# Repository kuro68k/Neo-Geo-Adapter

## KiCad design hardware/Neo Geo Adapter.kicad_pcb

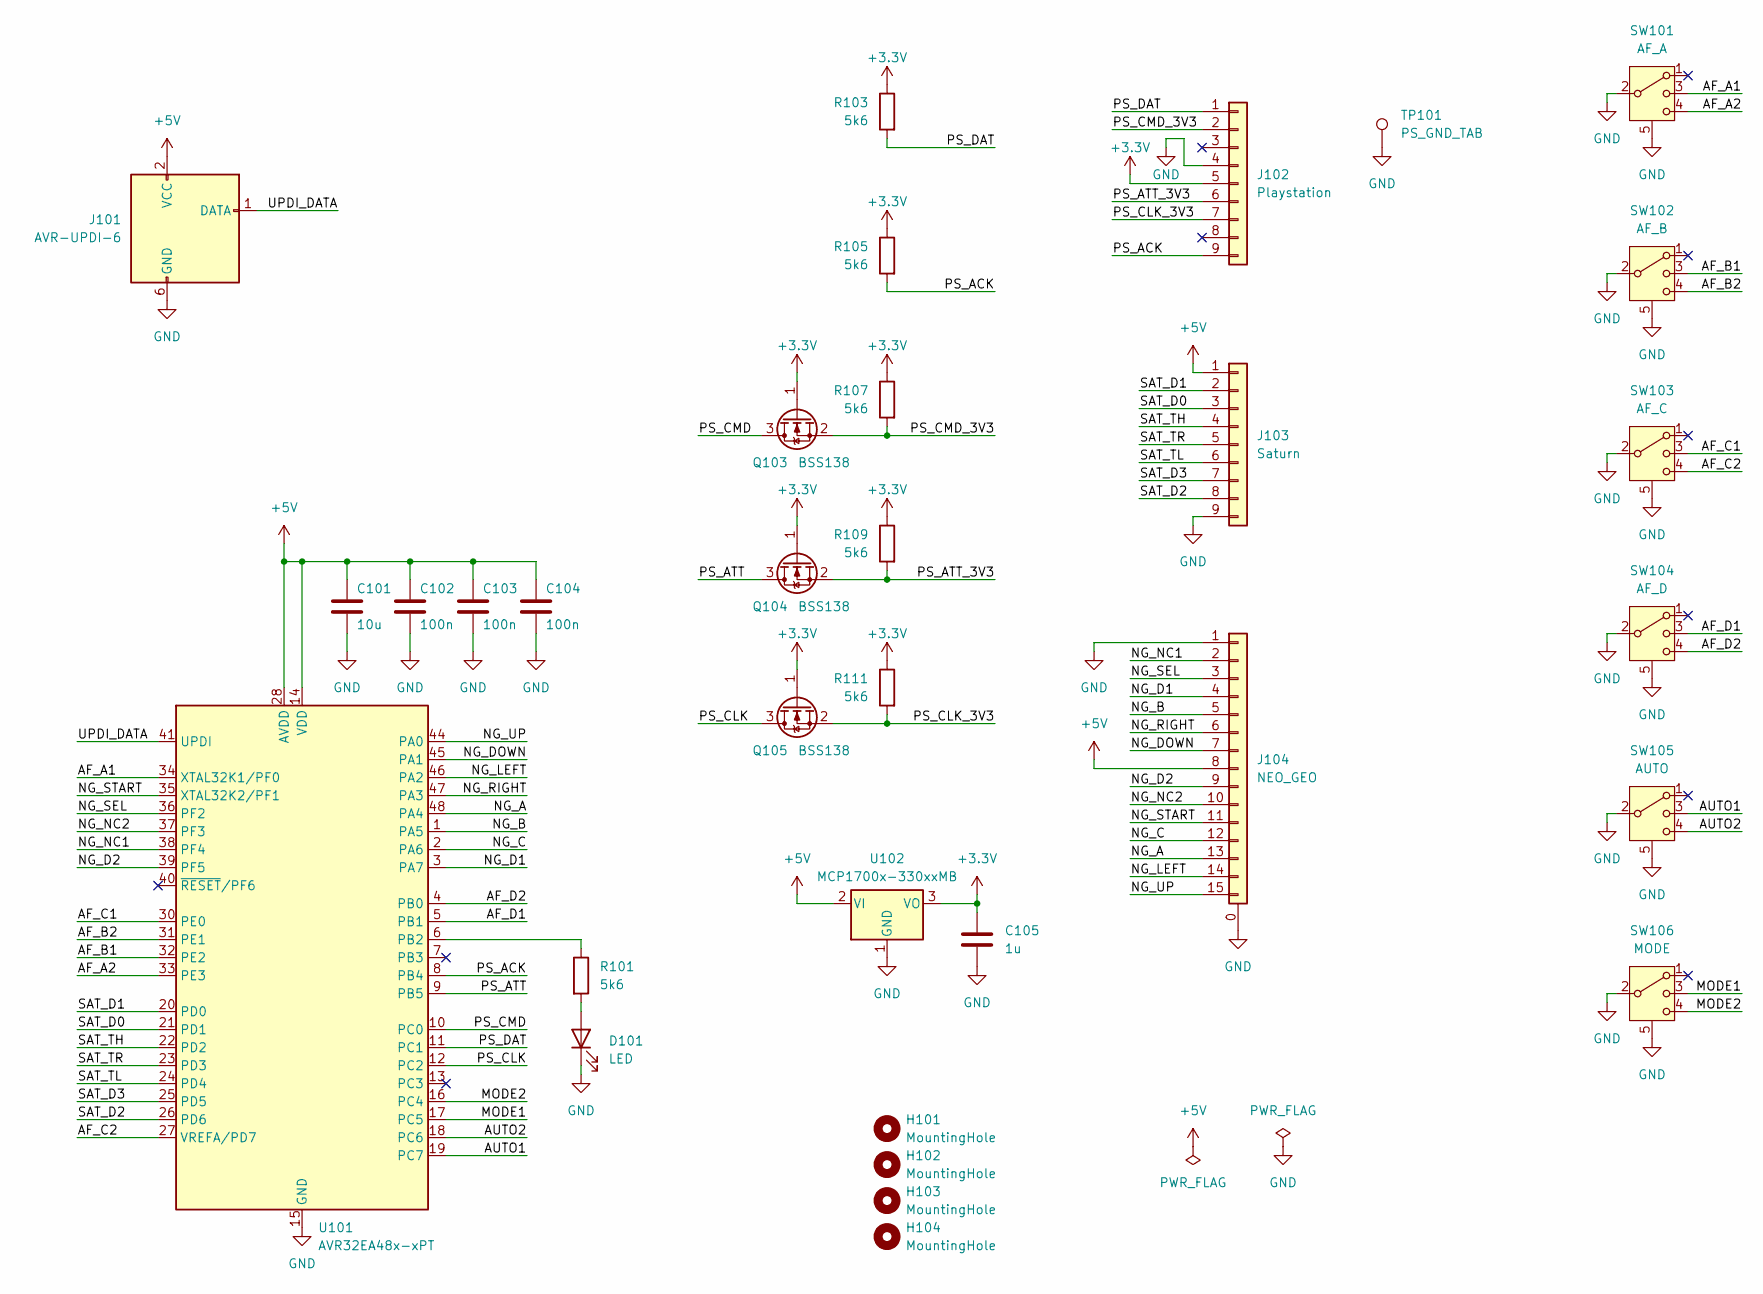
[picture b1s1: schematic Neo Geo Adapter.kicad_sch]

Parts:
C101: 10u; C_0805_2012Metric_Pad1.18x1.45mm_HandSolder
C102, C103, C104: 100n; C_0805_2012Metric_Pad1.18x1.45mm_HandSolder
C105: 1u; C_0805_2012Metric_Pad1.18x1.45mm_HandSolder
D101: LED; LED_0805_2012Metric_Pad1.15x1.40mm_HandSolder
H101, H102, H103, H104: MountingHole; MountingHole_3.2mm_M3
J101: AVR-UPDI-6; PinHeader_2x03_P1.27mm_Vertical_SMD
J102: Playstation; Sony_Playstation
J103: Saturn; Sega_Saturn
J104: NEO_GEO; DSUB-15_Female_Horizontal_P2.77x2.84mm_EdgePinOffset7.70mm_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; MPN Amphenol L77SDA15SA4CH4F
Q103, Q104, Q105: BSS138; SOT-23
R101, R103, R105, R107, R109, R111: 5k6; R_0805_2012Metric_Pad1.20x1.40mm_HandSolder
SW101: AF_A; XKB_SS13D75
SW102: AF_B; XKB_SS13D75
SW103: AF_C; XKB_SS13D75
SW104: AF_D; XKB_SS13D75
SW105: AUTO; XKB_SS13D75
SW106: MODE; XKB_SS13D75
TP101: PS_GND_TAB; TestPoint_THTPad_D2.5mm_Drill1.2mm
U101: AVR32EA48x-xPT; TQFP-48_7x7mm_P0.5mm
U102: MCP1700x-330xxMB; SOT-89-3

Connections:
+3.3V: C105.1, J102.5, Q103.1 (G), Q104.1 (G), Q105.1 (G), R103.1, R105.1, R107.1, R109.1, R111.1, U102.3 (VO)
+5V: C101.1, C102.1, C103.1, C104.1, J101.2 (VCC), J103.1, J104.8, U101.14 (VDD), U101.28 (AVDD), U101.42 (VDD), U102.2 (VI)
/AF_A1: SW101.3, U101.34 (XTAL32K1/PF0)
/AF_A2: SW101.4, U101.33 (PE3)
/AF_B1: SW102.3, U101.32 (PE2)
/AF_B2: SW102.4, U101.31 (PE1)
/AF_C1: SW103.3, U101.30 (PE0)
/AF_C2: SW103.4, U101.27 (VREFA/PD7)
/AF_D1: SW104.3, U101.5 (PB1)
/AF_D2: SW104.4, U101.4 (PB0)
/AUTO1: SW105.3, U101.19 (PC7)
/AUTO2: SW105.4, U101.18 (PC6)
/MODE1: SW106.3, U101.17 (PC5)
/MODE2: SW106.4, U101.16 (PC4)
/NG_A: J104.13, U101.48 (PA4)
/NG_B: J104.5, U101.1 (PA5)
/NG_C: J104.12, U101.2 (PA6)
/NG_D1: J104.4, U101.3 (PA7)
/NG_D2: J104.9, U101.39 (PF5)
/NG_DOWN: J104.7, U101.45 (PA1)
/NG_LEFT: J104.14, U101.46 (PA2)
/NG_NC1: J104.2, U101.38 (PF4)
/NG_NC2: J104.10, U101.37 (PF3)
/NG_RIGHT: J104.6, U101.47 (PA3)
/NG_SEL: J104.3, U101.36 (PF2)
/NG_START: J104.11, U101.35 (XTAL32K2/PF1)
/NG_UP: J104.15, U101.44 (PA0)
/PS_ACK: J102.9, R105.2, U101.8 (PB4)
/PS_ATT: Q104.3 (D), U101.9 (PB5)
/PS_ATT_3V3: J102.6, Q104.2 (S), R109.2
/PS_CLK: Q105.3 (D), U101.12 (PC2)
/PS_CLK_3V3: J102.7, Q105.2 (S), R111.2
/PS_CMD: Q103.3 (D), U101.10 (PC0)
/PS_CMD_3V3: J102.2, Q103.2 (S), R107.2
/PS_DAT: J102.1, R103.2, U101.11 (PC1)
/SAT_D0: J103.3, U101.21 (PD1)
/SAT_D1: J103.2, U101.20 (PD0)
/SAT_D2: J103.8, U101.26 (PD6)
/SAT_D3: J103.7, U101.25 (PD5)
/SAT_TH: J103.4, U101.22 (PD2)
/SAT_TL: J103.6, U101.24 (PD4)
/SAT_TR: J103.5, U101.23 (PD3)
/UPDI_DATA: J101.1 (DATA), U101.41 (UPDI)
GND: C101.2, C102.2, C103.2, C104.2, C105.2, D101.1 (K), J101.6 (GND), J102.4, J103.9, J104.0 (Shell), J104.1, SW101.2, SW101.5 (Shell), SW102.2, SW102.5 (Shell), SW103.2, SW103.5 (Shell), SW104.2, SW104.5 (Shell), SW105.2, SW105.5 (Shell), SW106.2, SW106.5 (Shell), TP101.1, U101.15 (GND), U101.29 (GND), U101.43 (GND), U102.1 (GND)
unnamed: D101.2 (A), R101.2
unnamed: R101.1, U101.6 (PB2)

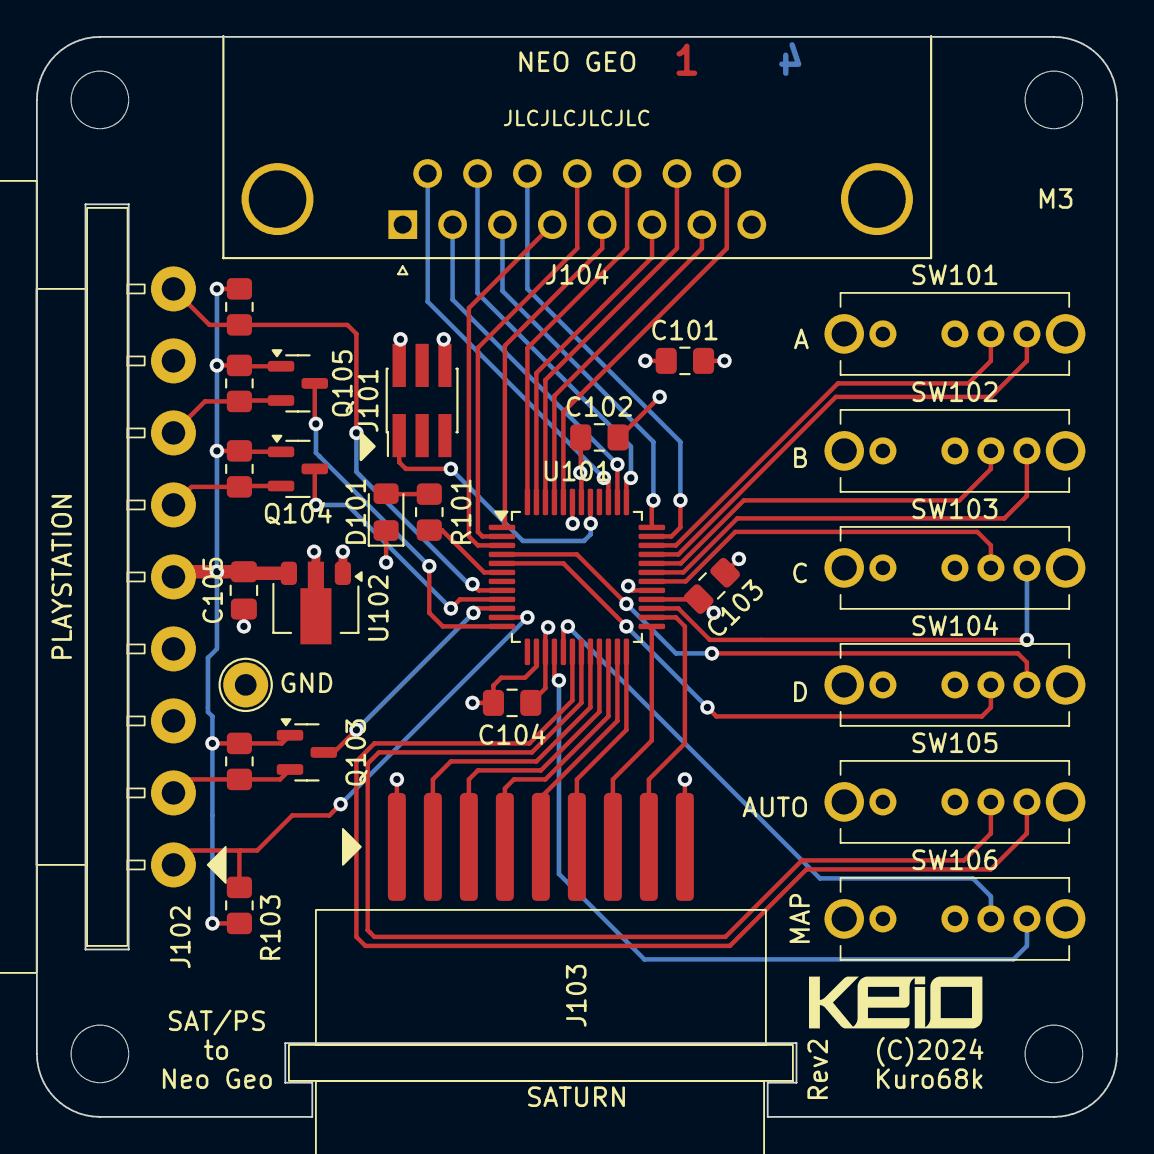
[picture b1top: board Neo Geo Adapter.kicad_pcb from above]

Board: 4 copper layers, 60.0 x 60.0 mm, 32 parts (0 on the bottom side), 46 nets.

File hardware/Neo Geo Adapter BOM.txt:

#	Reference		Qty	Value				Footprint
1	C101			1	10u					Capacitor_SMD:C_0805_2012Metric_Pad1.18x1.45mm_HandSolder	
2	C102,C103,C104	3	100n				Capacitor_SMD:C_0805_2012Metric_Pad1.18x1.45mm_HandSolder	
3	C105			1	1u					Capacitor_SMD:C_0805_2012Metric_Pad1.18x1.45mm_HandSolder	
4	D101			1	LED					LED_SMD:LED_0805_2012Metric_Pad1.15x1.40mm_HandSolder	
5	J101			1	AVR-UPDI-6			Connector_PinHeader_1.27mm:PinHeader_2x03_P1.27mm_Vertical_SMD	
6	J102			1	Playstation			Retro_Game_Connectors_3rd_Party:Sony_Playstation	
7	J103			1	Saturn				Retro_Game_Connectors_3rd_Party:Sega_Saturn	
8	J104			1	NEO_GEO				Connector_Dsub:DSUB-15_Female_Horizontal_P2.77x2.84mm_EdgePinOffset7.70mm_Housed_MountingHolesOffset9.12mm	
9	R101			1	470Ω				Resistor_SMD:R_0805_2012Metric_Pad1.20x1.40mm_HandSolder	
10	SW101			1	AF_A				Slide_Switch_TH:XKB_SS13D75	
11	SW102			1	AF_B				Slide_Switch_TH:XKB_SS13D75	
12	SW103			1	AF_C				Slide_Switch_TH:XKB_SS13D75	
13	SW104			1	AF_D				Slide_Switch_TH:XKB_SS13D75	
14	SW105			1	AUTO				Slide_Switch_TH:XKB_SS13D75	
15	SW106			1	MODE				Slide_Switch_TH:XKB_SS13D75	
16	U101			1	AVR32DA48x-xPT		Package_QFP:TQFP-48_7x7mm_P0.5mm	
17	U102			1	MCP1700x-330xxMB	Package_TO_SOT_SMD:SOT-89-3

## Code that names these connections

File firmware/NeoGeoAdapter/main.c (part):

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	PORTC.OUT =	PIN0_bm | PIN2_bm;			// SPI pins start high
	PORTC.DIR = PIN0_bm | PIN2_bm | PIN3_bm;
	PORTC.PIN1CTRL |= PORT_PULLUPEN_bm;		// PS DAT / MISO
	PORTC.PIN4CTRL |= PORT_PULLUPEN_bm;		// MODE2
	PORTC.PIN5CTRL |= PORT_PULLUPEN_bm;		// MODE1
	PORTC.PIN6CTRL |= PORT_PULLUPEN_bm;		// AUTO2
	PORTC.PIN7CTRL |= PORT_PULLUPEN_bm;		// AUTO2

	PORTD.OUT = SAT_TL_bm | SAT_TR_bm | SAT_TH_bm;
	PORTD.DIR = SAT_TL_bm | SAT_TR_bm | SAT_TH_bm;
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		SAT_PORT.OUTSET = SAT_TH_bm | SAT_TL_bm | SAT_TR_bm;
		// start PS comms
		//while (!(SPI.INTFLAGS & SPI_IF_bm));
		PS_ATT_PORT.OUTCLR = PS_ATT_PIN_bm;
		_delay_us(20);									// match PS timing

		// Saturn stage 1
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				ps_error = true;
		}
		
		PS_ATT_PORT.OUTSET = PS_ATT_PIN_bm;
		if (ps_error)
			ps_status1 = ps_status2 = 0;

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
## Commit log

2024-02-22 Autofire modes
2024-04-11 Fixed PDI header gender, KiCad 8
2024-04-11 Added BOM
2024-04-11 15 pin connector part and 3D model
2024-04-19 Added top board with labelling
2024-05-07 PCB artwork + output
2024-05-26 Saturn pad read OK
2024-05-28 All working
2024-05-29 Skip PS reading if not connected/error
2024-05-29 Set fuses, minimum watchdog timeout
2024-06-03 Playstation 3V3 power and signalling
2024-08-27 Rev 2 RTM

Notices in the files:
hardware/Neo Geo Adapter.kicad_pcb:
(C)2024
